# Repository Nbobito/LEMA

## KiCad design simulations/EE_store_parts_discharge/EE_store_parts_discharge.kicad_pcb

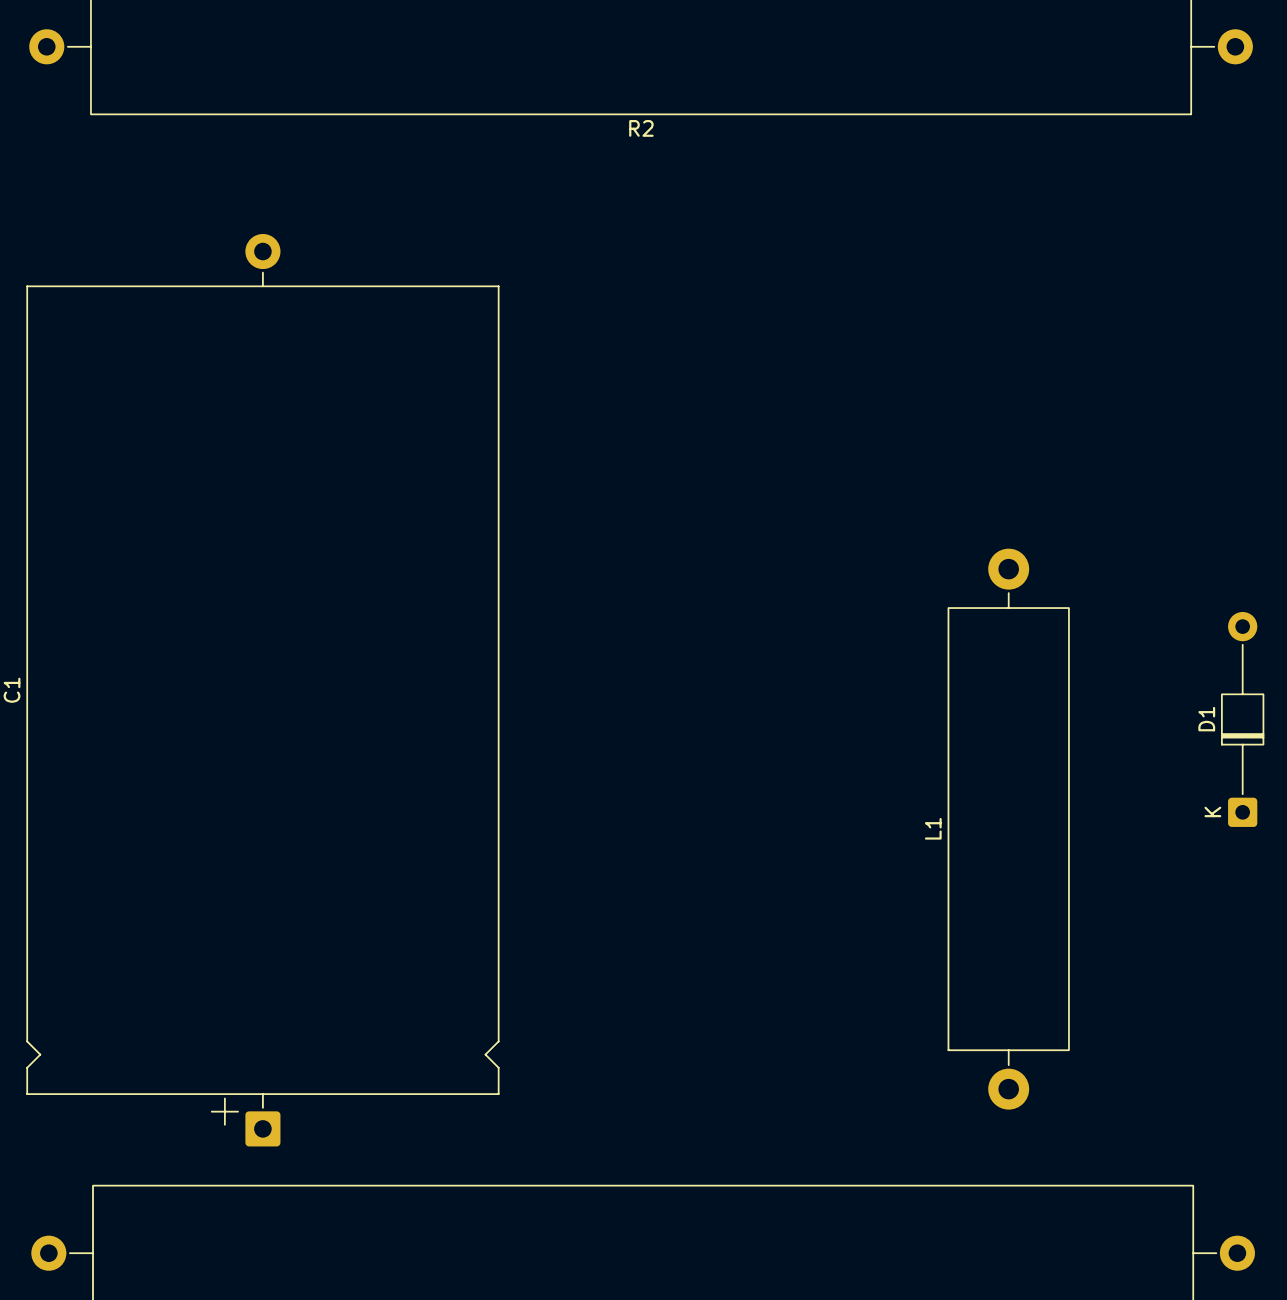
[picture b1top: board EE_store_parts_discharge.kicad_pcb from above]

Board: 2 copper layers, 5 parts (0 on the bottom side), 4 nets, no tracks yet.

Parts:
C1: 2200u; CP_Axial_L55.0mm_D32.0mm_P60.00mm_Horizontal
D1: D; D_T-1_P12.70mm_Horizontal
L1: 200u; L_Axial_L30.0mm_D8.0mm_P35.56mm_Horizontal_Fastron_77A
R1: 0.1; R_Axial_Power_L75.0mm_W9.0mm_P81.28mm
R2: 0.01; R_Axial_Power_L75.0mm_W9.0mm_P81.28mm

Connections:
/VC1: C1.1, R1.2
GND: C1.2, R2.2
unnamed: D1.2 (A), L1.2, R2.1
unnamed: D1.1 (K), L1.1, R1.1
